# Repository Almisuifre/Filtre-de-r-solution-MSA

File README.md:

# Filtre-de-r-solution-MSA
Filtre de Résolution MSA

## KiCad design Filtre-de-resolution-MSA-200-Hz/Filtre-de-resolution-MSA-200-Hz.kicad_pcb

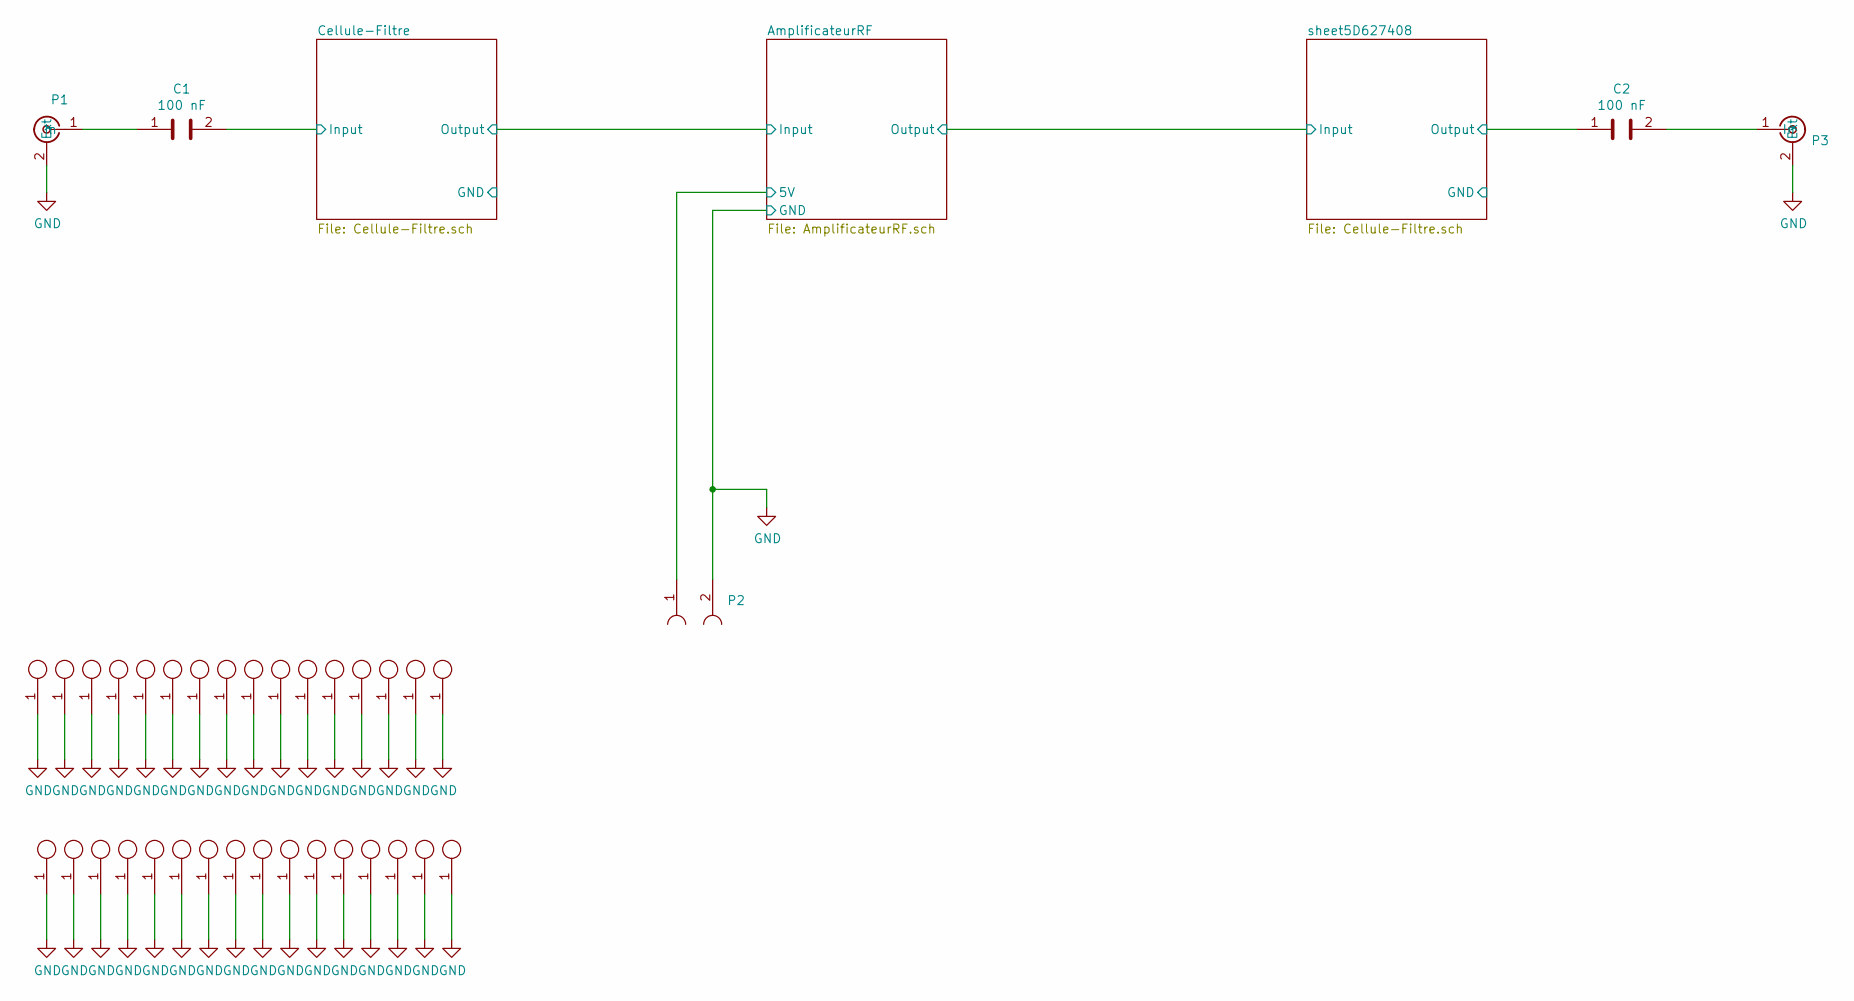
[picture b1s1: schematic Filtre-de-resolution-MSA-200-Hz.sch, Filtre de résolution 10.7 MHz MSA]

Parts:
C1, C2: 100 nF; condensateur_0805
P1, P3: SMA; SMA_Molex_73251-2200_Horizontal
P2: Connecteur2Pin; Connec_Mal_2-54_1x2
VG1, VG2, VG3, VG4, VG5, VG6, VG7, VG8, VG9, VG10, VG11, VG12, VG13, VG14, VG15, VG16, VG17, VG18, VG19, VG20, VG21, VG22, VG23, VG24, VG25, VG26, VG27, VG28, VG29, VG30, VG31, VG32: ViaGround

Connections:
/AmplificateurRF/5V: P2.1; also elsewhere on the board
/Cellule-Filtre/Input: C1.2; also elsewhere on the board
/sheet5D627408/Output: C2.1; also elsewhere on the board
GND: P1.2 (Ext), P2.2, P3.2 (Ext), VG1.1, VG2.1, VG3.1, VG4.1, VG5.1, VG6.1, VG7.1, VG8.1, VG9.1, VG10.1, VG11.1, VG12.1, VG13.1, VG14.1, VG15.1, VG16.1, VG17.1, VG18.1, VG19.1, VG20.1, VG21.1, VG22.1, VG23.1, VG24.1, VG25.1, VG26.1, VG27.1, VG28.1, VG29.1, VG30.1, VG31.1, VG32.1; also elsewhere on the board
unnamed: C1.1, P1.1 (In)
unnamed: C2.2, P3.1 (In)

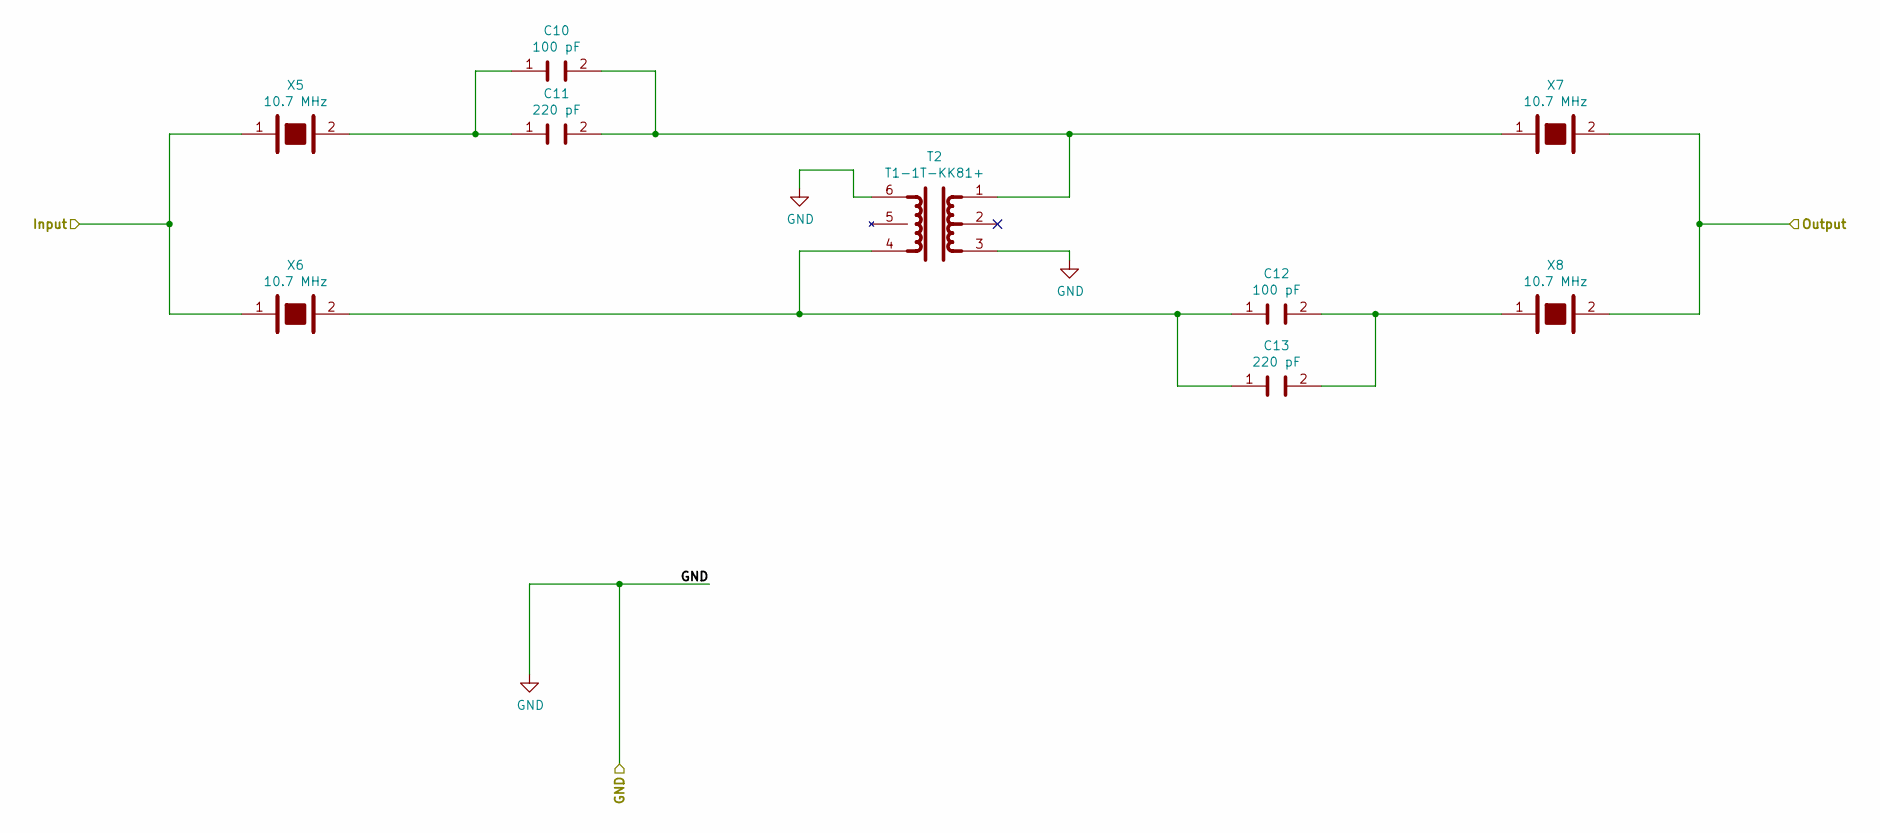
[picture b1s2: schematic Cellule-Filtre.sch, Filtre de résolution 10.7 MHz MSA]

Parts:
C3, C5: 100 pF; condensateur_0805
C4, C6: 220 pF; condensateur_0805
T1: T1-1T-KK81+; T1-1I-KK81_plus
X1, X2, X3, X4: 10.7 MHz; quartz-HC48_HC49

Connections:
/AmplificateurRF/Input: X3.2, X4.2; also elsewhere on the board
/Cellule-Filtre/Input: X1.1, X2.1; also elsewhere on the board
GND: T1.3, T1.6; also elsewhere on the board
unnamed: C3.1, C4.1, X1.2
unnamed: C3.2, C4.2, T1.1, X3.1
unnamed: C5.1, C6.1, T1.4, X2.2
unnamed: C5.2, C6.2, X4.1

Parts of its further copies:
C10, C12: 100 pF; condensateur_0805
C11, C13: 220 pF; condensateur_0805
T2: T1-1T-KK81+; T1-1I-KK81_plus
X5, X6, X7, X8: 10.7 MHz; quartz-HC48_HC49

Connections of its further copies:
/sheet5D627408/Input: X5.1, X6.1; also elsewhere on the board
/sheet5D627408/Output: X7.2, X8.2; also elsewhere on the board
GND: T2.3, T2.6; also elsewhere on the board
unnamed: C10.1, C11.1, X5.2
unnamed: C10.2, C11.2, T2.1, X7.1
unnamed: C12.1, C13.1, T2.4, X6.2
unnamed: C12.2, C13.2, X8.1

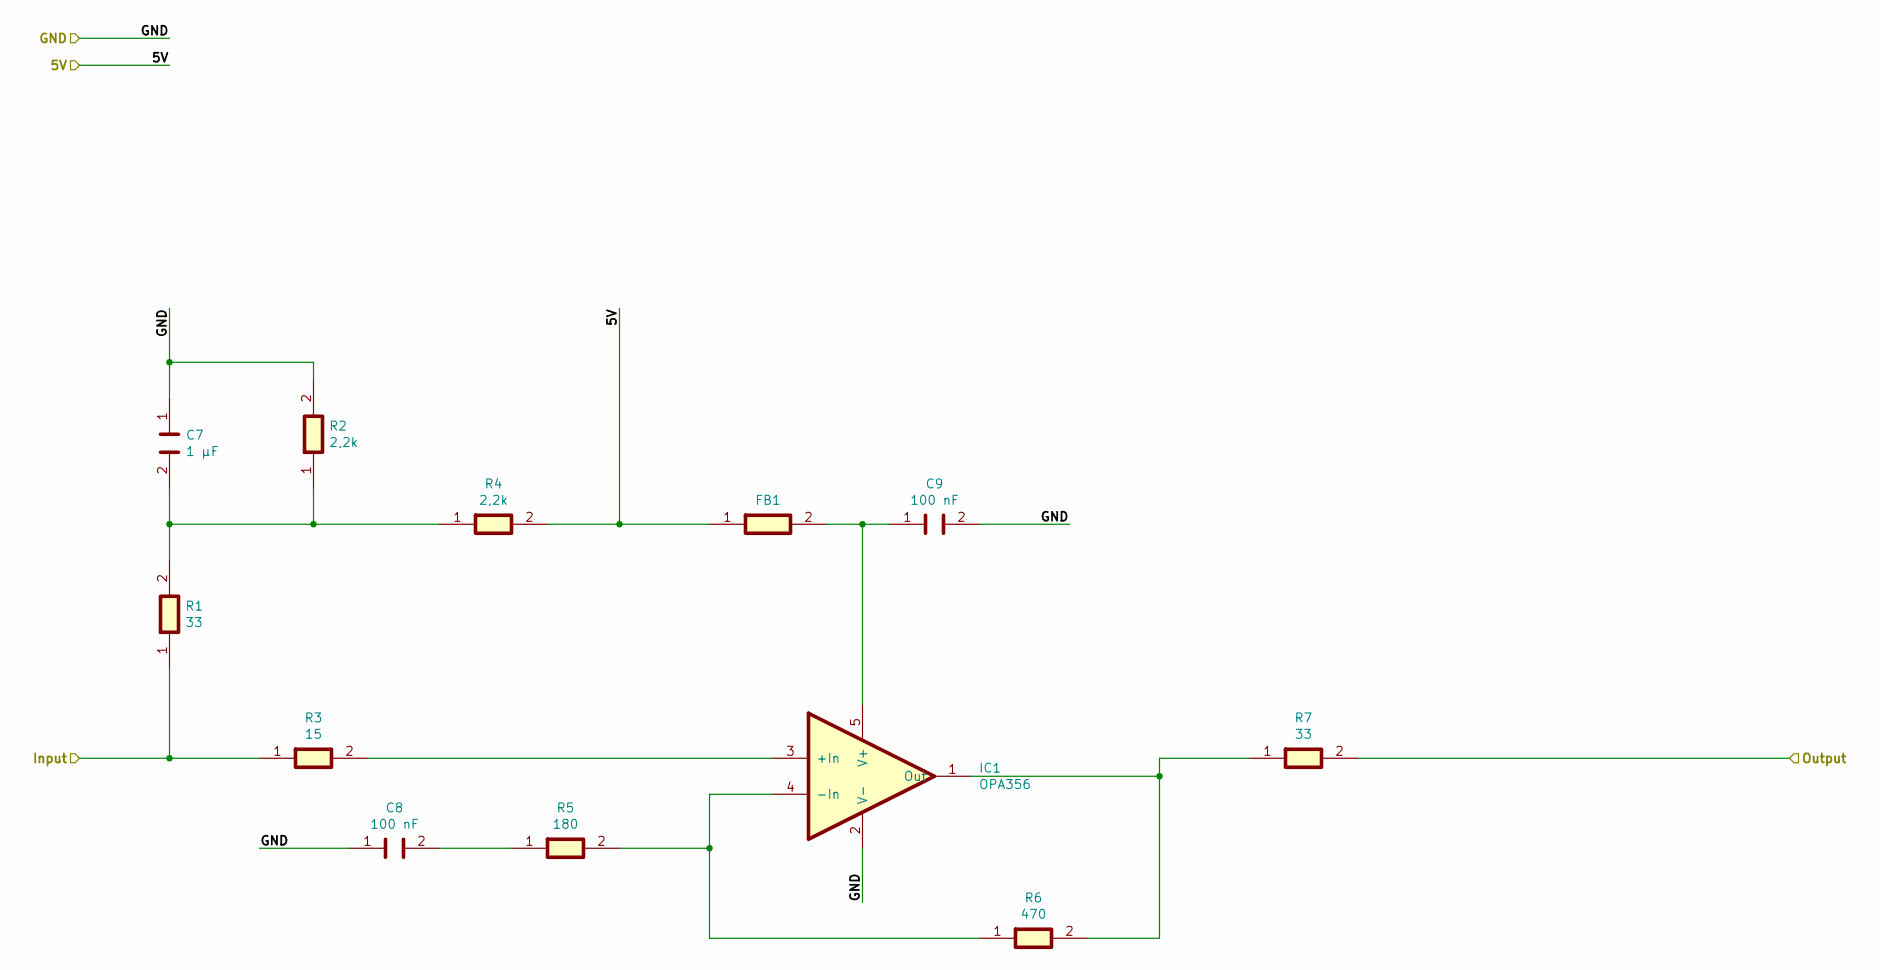
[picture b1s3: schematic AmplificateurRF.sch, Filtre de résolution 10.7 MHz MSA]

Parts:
C7: 1 µF; condensateur_0805
C8, C9: 100 nF; condensateur_0805
FB1: FeriteBead; FB_0805
IC1: OPA356; SOT-23
R1, R7: 33; resistance_0805
R2, R4: 2,2k; resistance_0805
R3: 15; resistance_0805
R5: 180; resistance_0805
R6: 470; resistance_0805

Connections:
/AmplificateurRF/5V: FB1.1, R4.2; also elsewhere on the board
/AmplificateurRF/Input: R1.1, R3.1; also elsewhere on the board
/sheet5D627408/Input: R7.2; also elsewhere on the board
GND: C7.1, C8.1, C9.2, IC1.2 (V-), R2.2; also elsewhere on the board
unnamed: C7.2, R1.2, R2.1, R4.1
unnamed: C8.2, R5.1
unnamed: C9.1, FB1.2, IC1.5 (V+)
unnamed: IC1.1 (Out), R6.2, R7.1
unnamed: IC1.3 (+In), R3.2
unnamed: IC1.4 (-In), R5.2, R6.1

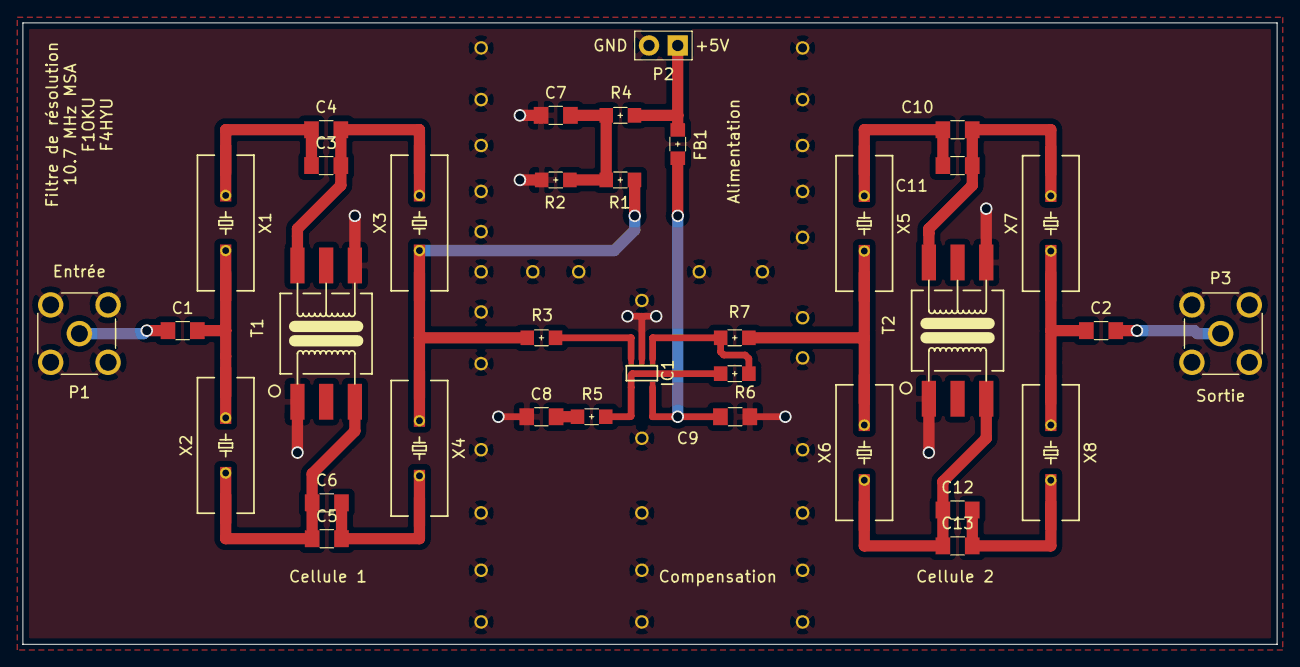
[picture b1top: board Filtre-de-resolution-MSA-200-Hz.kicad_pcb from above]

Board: 2 copper layers, 111.0 x 55.0 mm, 67 parts (0 on the bottom side), 22 nets.

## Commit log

2019-08-24 Create project filter 10.7 MHz
    Create project filter 10.7 MHz
    Create library
    Create 3D library
    Create Schema
    Create Position of component
2019-08-24 Update project
    Update Schematic and PCB
    Add a new library
2019-08-24 Update project
    Modifi a files PDF
2019-08-28 Update project
    Add sheet of values of component to the soldering
